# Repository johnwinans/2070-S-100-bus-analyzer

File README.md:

# 2070-S-100-bus-analyzer

A 120 channel S-100 bus logic analyzer

This project is based on the open source ["gusmanb" Logic Analyzer](https://github.com/gusmanb/logicanalyzer) project from Agustín Gimenez Bernad

I have started a [YouTube playlist](https://www.youtube.com/playlist?list=PL3by7evD3F51xCtWdVP3EZzuDttMwDS_U) of videos about this project and my testing of the board.

By using the software from the gusmanb/logicanalyzer repo, a 120 channel logic analyzer can be assembled by installing 5 Raspberry PI PICO boards on this S-100 card and accessed using a USB cables to a PC and/or WiFi as described in the above gusmanb github project Wiki.

Here is a [CSV of the project BOM](./2070-S-100-bus-analyzer.csv) with Digikey order numbers. 

NOTE: I used generic male-headers that I got on Amazon and snapped to length.  I only use gold-plated headers.  Anything else is annoying.
Here is a link to the type that I use for most everything: https://a.co/d/02YRvqt7 (Hint: I snap them to length using a flat [Hakko Wire Cutters](https://a.co/d/055L9axg). Then use shunts to hold them in pairs, triples, or whatever you need so they stay straight and aligned when soldering.)

# Rev 1.0

***NOTICE: As of April 20, 2026 Rev 1.0 of this design has been tested and is a fully functional board.  However, I am making some cosmetic tweaks (silkscreen, better testpoints, and I might shorten the PCB by 1/8"... see my self-critique in the above playlist.)  I will post a release (and remove this message) when I consider it in final form.***

# Rev 2.0

***NOTE: This is a release in progress.  It has not yet been tested.***

## Changes
- Change the board height to 5.0 inches to better fit into IEEE card cages.
- Change to use 3-row headers so that signals can be connected to a trigger input at the same time as the normal analyzedr channel with simpler jumper wires.
- Remove the alternate regulator option.
- Add special headers for pins 20 and 70 to make their purpose more obvious.
- Change to use thru-hole ground test-points for easier use with gator-clips.
- Use larger fonts and better-center the signal names.

# Ordering from JLCPCB

Last time I ordered these, right or wrong, I used these JLCPCB settings:

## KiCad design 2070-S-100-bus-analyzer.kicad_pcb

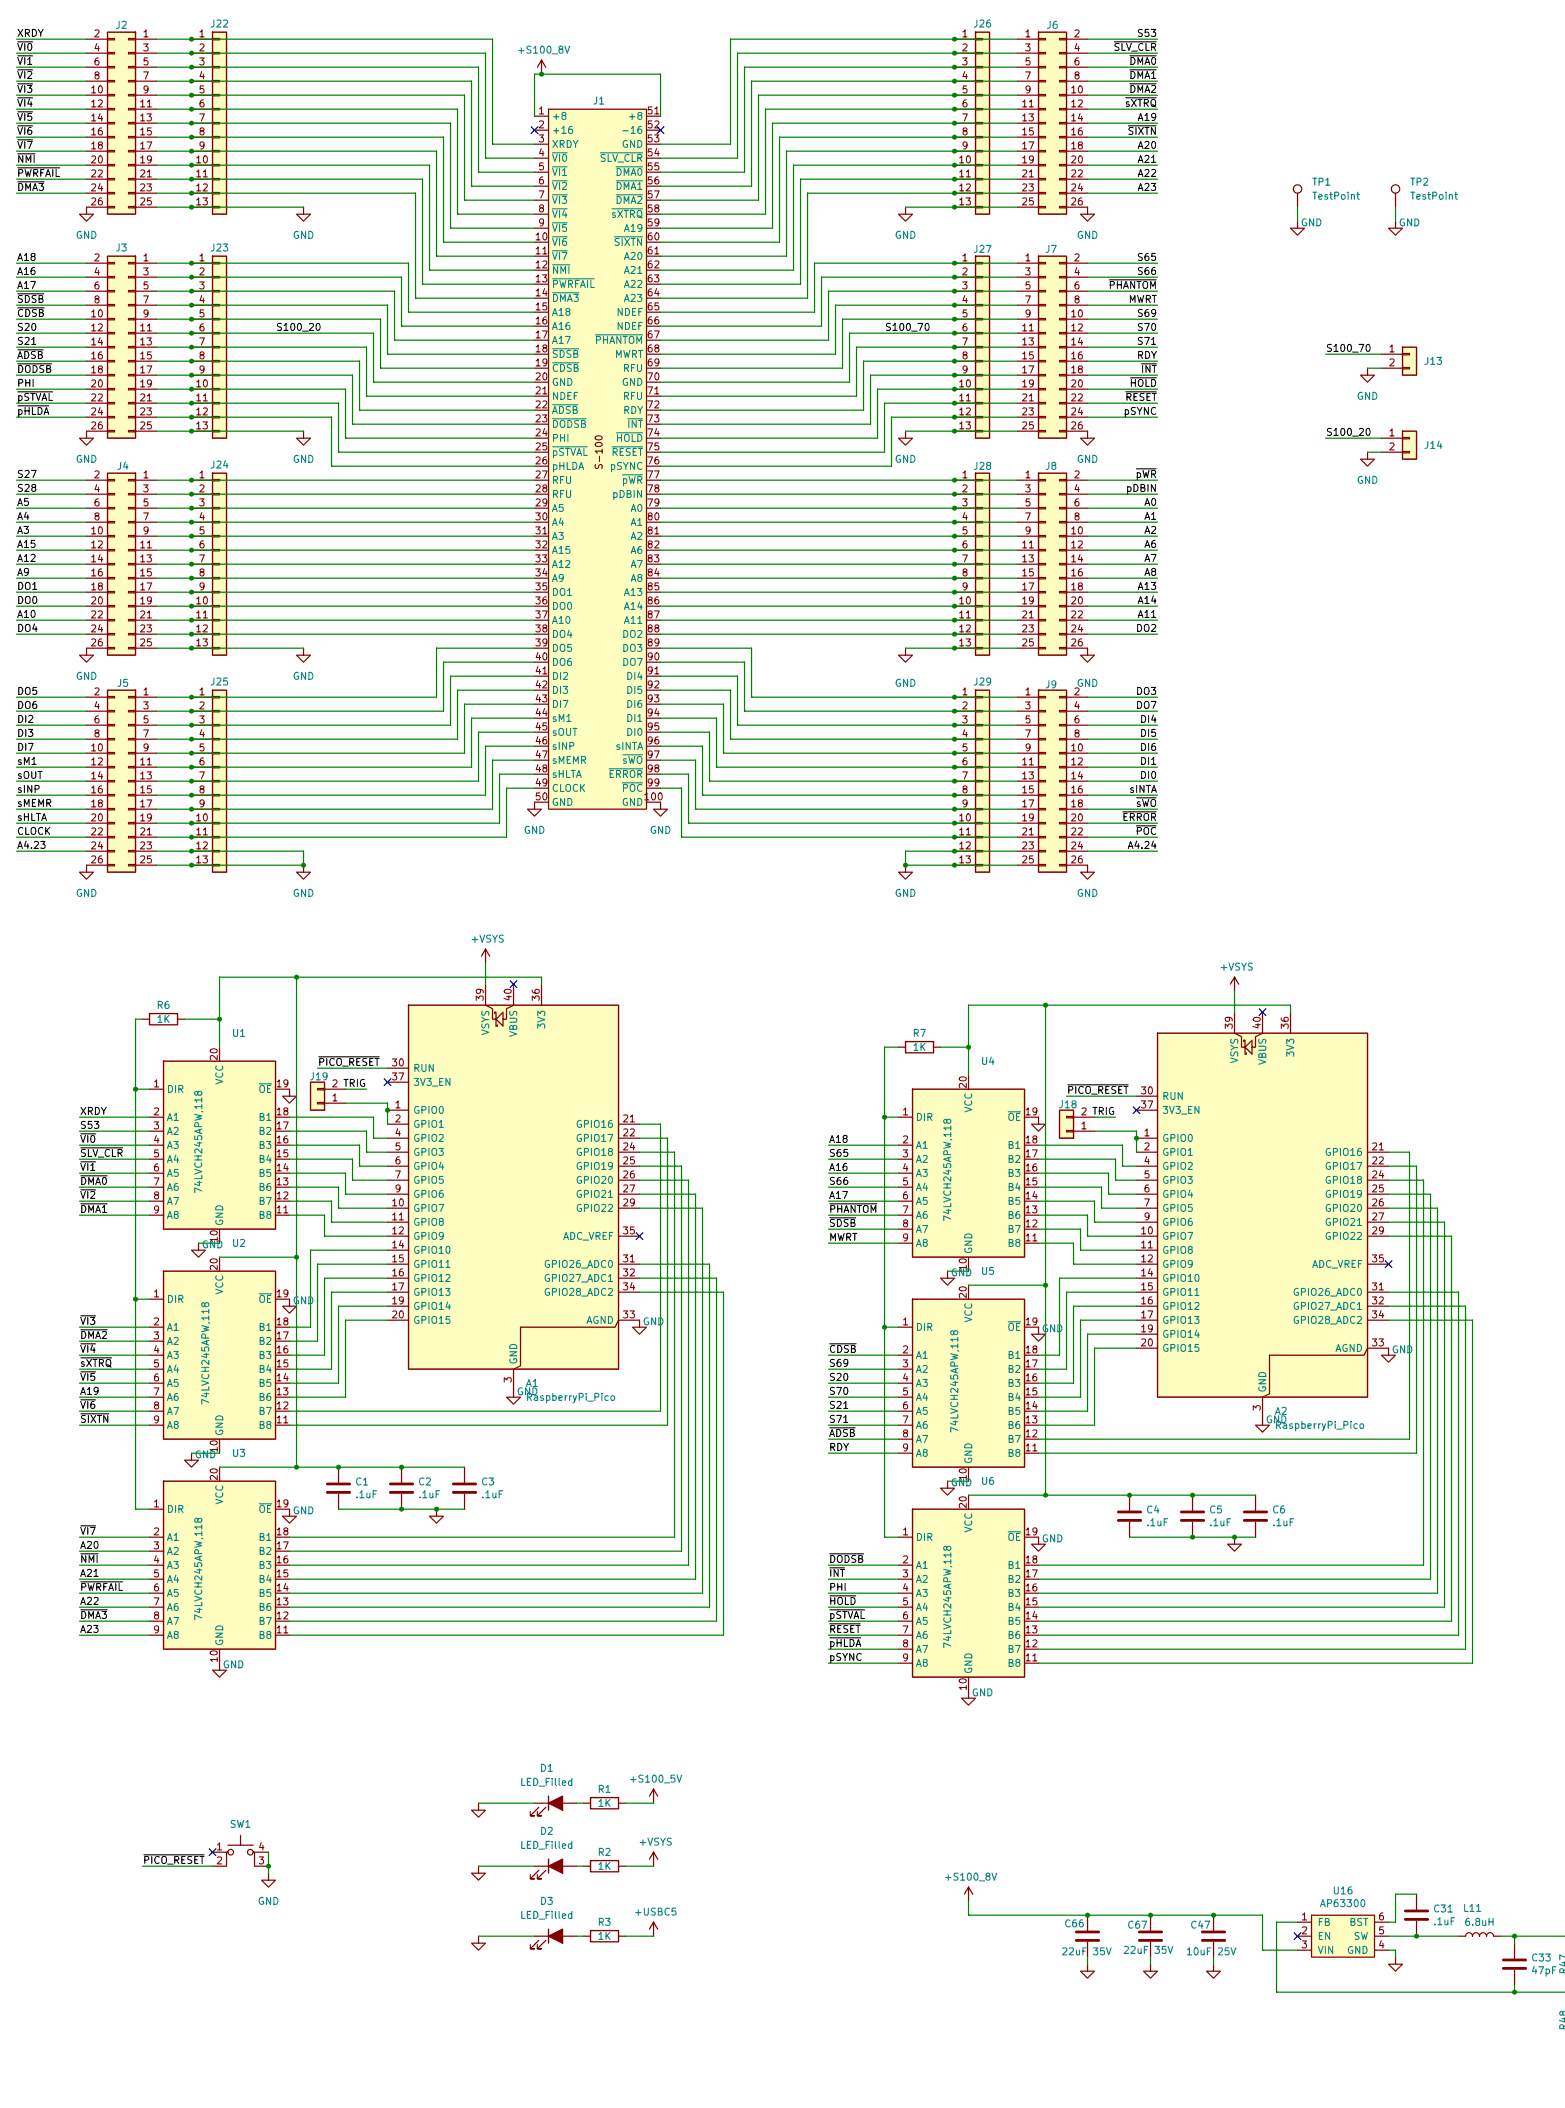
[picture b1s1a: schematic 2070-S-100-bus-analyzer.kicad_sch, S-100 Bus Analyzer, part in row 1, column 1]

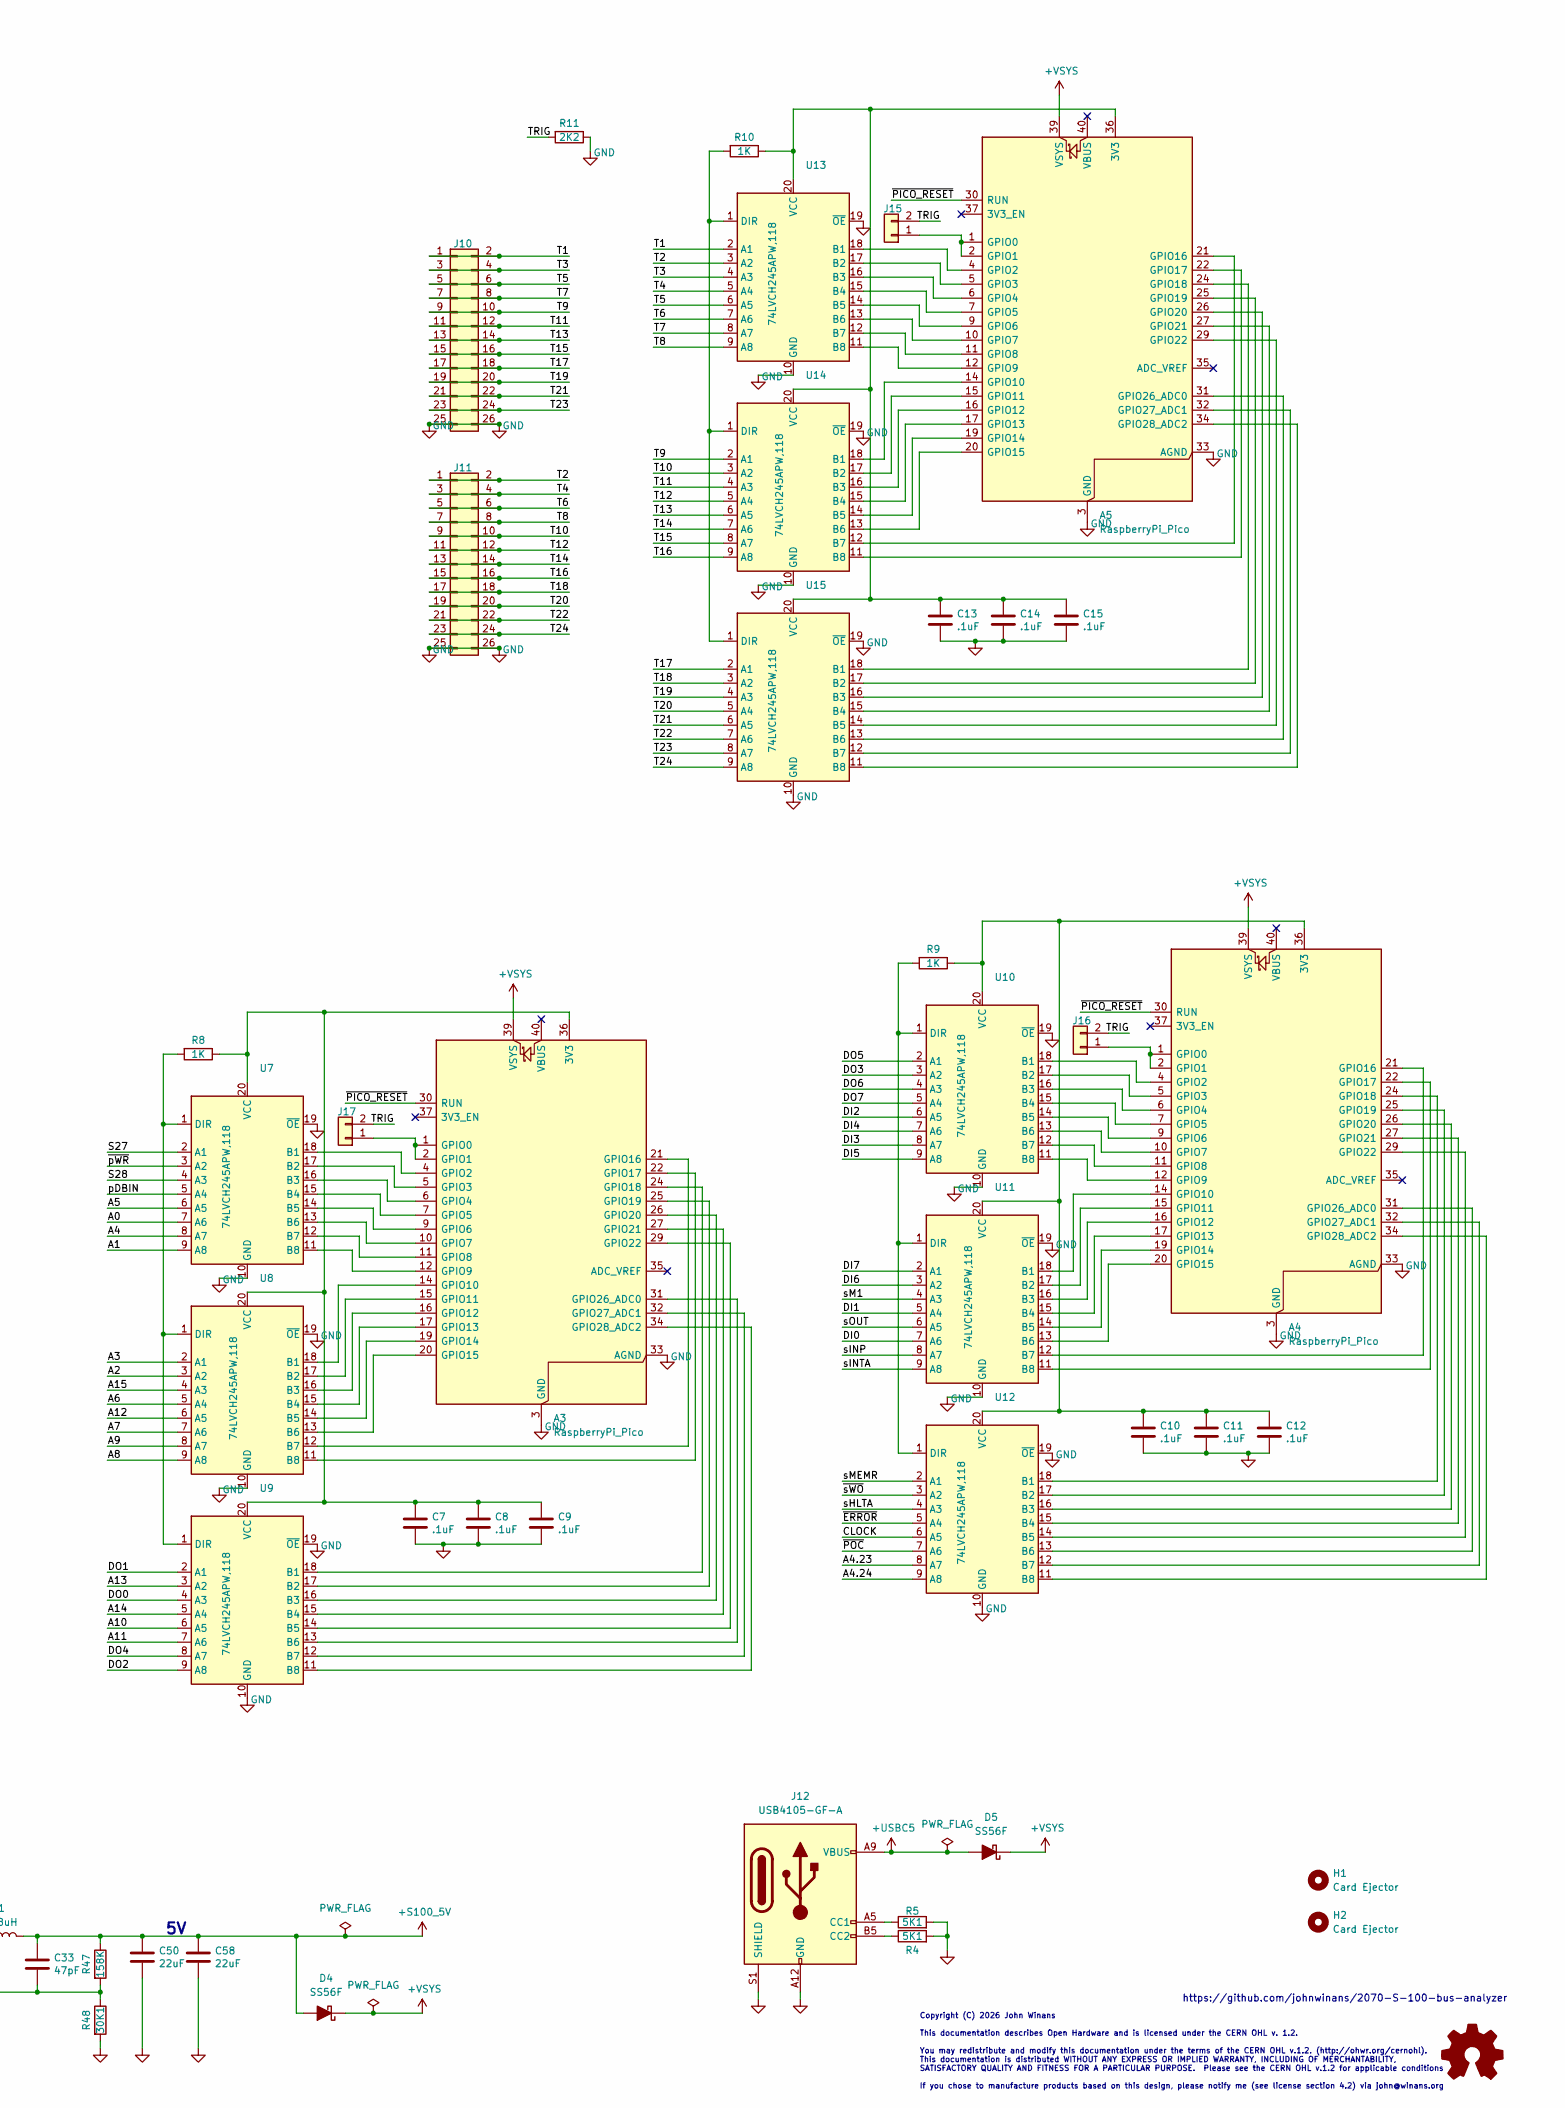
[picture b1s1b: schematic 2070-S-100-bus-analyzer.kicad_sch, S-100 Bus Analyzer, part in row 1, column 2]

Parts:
A1, A2, A3, A4, A5: RaspberryPi_Pico; RaspberryPi_Pico_Common_Unspecified; MPN 2648-SC1631CT-ND; Digi-Key_PN 2648-SC1631CT-ND
C1, C2, C3, C4, C5, C6, C7, C8, C9, C10, C11, C12, C13, C14, C15, C31: .1uF; C_0603_1608Metric_Pad1.08x0.95mm_HandSolder; MPN C1608X5R1E104K; Digi-Key_PN 445-6854-1-ND
C33: 47pF; C_0603_1608Metric_Pad1.08x0.95mm_HandSolder; MPN CL10C470JB8NNNC; Digi-Key_PN 1276-1037-1-ND
C47: 10uF 25V; C_0805_2012Metric_Pad1.18x1.45mm_HandSolder; MPN TMK212BBJ106KG-T; Digi-Key_PN 587-2985-1-ND
C50, C58: 22uF; C_0805_2012Metric_Pad1.18x1.45mm_HandSolder; MPN GRM21BR61A226ME44L; Digi-Key_PN 490-10746-1-ND
C66, C67: 22uF 35V; C_0805_2012Metric_Pad1.18x1.45mm_HandSolder; MPN C2012X5R1V226M125AC; Digi-Key_PN 445-14428-1-ND
D1, D2, D3: LED_Filled; LED_0805_2012Metric_Pad1.15x1.40mm_HandSolder; MPN LG R971-KN-1-0-20-R18; Digi-Key_PN 475-LGR971-KN-1CT-ND
D4, D5: SS56F; D_SMB; MPN SS56F; Digi-Key_PN 5399-SS56FCT-ND
H1, H2: Card Ejector; MountingHole_2.5mm; MPN CP-26 WE; Digi-Key_PN 492-1025-ND
J1: S-100 Edge Connector; S100-Edge-Connector
J2, J3, J4, J5, J6, J7, J8, J9, J10, J11: Conn_02x13_Odd_Even; PinHeader_2x13_P2.54mm_Vertical
J12: USB4105-GF-A; USB_C_Receptacle_GCT_USB4105-xx-A_16P_TopMnt_Horizontal; MPN USB4105-GF-A; Digi-Key_PN 2073-USB4105-GF-ACT-ND
J13, J14, J15, J16, J17, J18, J19: Conn_01x02; PinHeader_1x02_P2.54mm_Vertical
J22, J23, J24, J25, J26, J27, J28, J29: Conn_01x13; PinHeader_1x13_P2.54mm_Vertical
L11: 6.8uH; L_Bourns-SRN6028; MPN VLS6045EX-6R8M; Digi-Key_PN 445-173057-1-ND
LOGO1: OSHW_Logo; OSHW-Logo_11.4x12mm_SilkScreen
R1, R2, R3, R6, R7, R8, R9, R10: 1K; R_0603_1608Metric_Pad0.98x0.95mm_HandSolder; MPN RC0603FR-071KL; Digi-Key_PN 311-1.00KHRCT-ND
R4, R5: 5K1; R_0603_1608Metric_Pad0.98x0.95mm_HandSolder; MPN CR0603-FX-5110ELF; Digi-Key_PN CR0603-FX-510ELFCT-ND
R11: 2K2; R_0603_1608Metric_Pad0.98x0.95mm_HandSolder; MPN RC0603FR-072K2L; Digi-Key_PN 311-2.20KHRCT-ND
R47: 158K; R_0603_1608Metric_Pad0.98x0.95mm_HandSolder; MPN RT0603FRE07158KL; Digi-Key_PN 13-RT0603FRE07158KLCT-ND
R48: 30K1; R_0603_1608Metric_Pad0.98x0.95mm_HandSolder; MPN RT0603FRE0730K1L; Digi-Key_PN 13-RT0603FRE0730K1LCT-ND
SW1: SW_MEC_5E; tactile; MPN 1-1825910-5; Digi-Key_PN 450-1940-ND
TP1, TP2: TestPoint; TestPoint_Keystone_5010-5014_Multipurpose; Digi-Key_PN 2019-RCWCTECT-ND
U1, U2, U3, U4, U5, U6, U7, U8, U9, U10, U11, U12, U13, U14, U15: 74LVCH245APW,118; TSSOP-20_4.4x6.5mm_P0.65mm; MPN 74LVCH245APW,118; Digi-Key_PN 1727-4041-1-ND
U16: AP63300; SOT-23-6; MPN AP63301WU-7; Digi-Key_PN 31-AP63301WU-7CT-ND

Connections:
+S100_5V: C33.1, C50.1, C58.1, D4.2 (A), L11.2, R1.1, R47.1
+S100_8V: C47.1, C66.1, C67.1, J1.1 (+8), J1.51 (+8), U16.3 (VIN)
+USBC5: D5.2 (A), J12.A4 (VBUS), J12.A9 (VBUS), J12.B4 (VBUS), J12.B9 (VBUS), R3.1
+VSYS: A1.39 (VSYS), A2.39 (VSYS), A3.39 (VSYS), A4.39 (VSYS), A5.39 (VSYS), D4.1 (K), D5.1 (K), R2.1
/A0: J8.6, U7.7 (A6)
/A1: J8.8, U7.9 (A8)
/A2: J8.10, U8.3 (A2)
/A3: J4.10, U8.2 (A1)
/A4: J4.8, U7.8 (A7)
/A4.23: J5.24, U12.8 (A7)
/A4.24: J9.24, U12.9 (A8)
/A5: J4.6, U7.6 (A5)
/A6: J8.12, U8.5 (A4)
/A7: J8.14, U8.7 (A6)
/A8: J8.16, U8.9 (A8)
/A9: J4.16, U8.8 (A7)
/A10: J4.22, U9.6 (A5)
/A11: J8.22, U9.7 (A6)
/A12: J4.14, U8.6 (A5)
/A13: J8.18, U9.3 (A2)
/A14: J8.20, U9.5 (A4)
/A15: J4.12, U8.4 (A3)
/A16: J3.4, U4.4 (A3)
/A17: J3.6, U4.6 (A5)
/A18: J3.2, U4.2 (A1)
/A19: J6.14, U2.7 (A6)
/A20: J6.18, U3.3 (A2)
/A21: J6.20, U3.5 (A4)
/A22: J6.22, U3.7 (A6)
/A23: J6.24, U3.9 (A8)
/CLOCK: J5.22, U12.6 (A5)
/DI0: J9.14, U11.7 (A6)
/DI1: J9.12, U11.5 (A4)
/DI2: J5.6, U10.6 (A5)
/DI3: J5.8, U10.8 (A7)
/DI4: J9.6, U10.7 (A6)
/DI5: J9.8, U10.9 (A8)
/DI6: J9.10, U11.3 (A2)
/DI7: J5.10, U11.2 (A1)
/DO0: J4.20, U9.4 (A3)
/DO1: J4.18, U9.2 (A1)
/DO2: J8.24, U9.9 (A8)
/DO3: J9.2, U10.3 (A2)
/DO4: J4.24, U9.8 (A7)
/DO5: J5.2, U10.2 (A1)
/DO6: J5.4, U10.4 (A3)
/DO7: J9.4, U10.5 (A4)
/MWRT: J7.8, U4.9 (A8)
/PHI: J3.20, U6.4 (A3)
/RDY: J7.16, U5.9 (A8)
/S20: J3.12, U5.4 (A3)
/S21: J3.14, U5.6 (A5)
/S27: J4.2, U7.2 (A1)
/S28: J4.4, U7.4 (A3)
/S53: J6.2, U1.3 (A2)
/S65: J7.2, U4.3 (A2)
/S66: J7.4, U4.5 (A4)
/S69: J7.10, U5.3 (A2)
/S70: J7.12, U5.5 (A4)
/S71: J7.14, U5.7 (A6)
/S100_20: J1.20 (GND), J3.11, J14.1, J23.6
/S100_70: J1.70 (GND), J7.11, J13.1, J27.6
/T1: J10.1, J10.2, U13.2 (A1)
/T2: J11.1, J11.2, U13.3 (A2)
/T3: J10.3, J10.4, U13.4 (A3)
/T4: J11.3, J11.4, U13.5 (A4)
/T5: J10.5, J10.6, U13.6 (A5)
/T6: J11.5, J11.6, U13.7 (A6)
/T7: J10.7, J10.8, U13.8 (A7)
/T8: J11.7, J11.8, U13.9 (A8)
/T9: J10.9, J10.10, U14.2 (A1)
/T10: J11.9, J11.10, U14.3 (A2)
/T11: J10.11, J10.12, U14.4 (A3)
/T12: J11.11, J11.12, U14.5 (A4)
/T13: J10.13, J10.14, U14.6 (A5)
/T14: J11.13, J11.14, U14.7 (A6)
/T15: J10.15, J10.16, U14.8 (A7)
/T16: J11.15, J11.16, U14.9 (A8)
/T17: J10.17, J10.18, U15.2 (A1)
/T18: J11.17, J11.18, U15.3 (A2)
/T19: J10.19, J10.20, U15.4 (A3)
/T20: J11.19, J11.20, U15.5 (A4)
/T21: J10.21, J10.22, U15.6 (A5)
/T22: J11.21, J11.22, U15.7 (A6)
/T23: J10.23, J10.24, U15.8 (A7)
/T24: J11.23, J11.24, U15.9 (A8)
/TRIG: J15.2, J16.2, J17.2, J18.2, J19.2, R11.2
/XRDY: J2.2, U1.2 (A1)
/pDBIN: J8.4, U7.5 (A4)
/pSYNC: J7.24, U6.9 (A8)
/sHLTA: J5.20, U12.4 (A3)
/sINP: J5.16, U11.8 (A7)
/sINTA: J9.16, U11.9 (A8)
/sM1: J5.12, U11.4 (A3)
/sMEMR: J5.18, U12.2 (A1)
/sOUT: J5.14, U11.6 (A5)
/~ADSB: J3.16, U5.8 (A7)
/~CDSB: J3.10, U5.2 (A1)
/~DMA0: J6.6, U1.7 (A6)
/~DMA1: J6.8, U1.9 (A8)
/~DMA2: J6.10, U2.3 (A2)
/~DMA3: J2.24, U3.8 (A7)
/~DODSB: J3.18, U6.2 (A1)
/~ERROR: J9.20, U12.5 (A4)
/~HOLD: J7.20, U6.5 (A4)
/~INT: J7.18, U6.3 (A2)
/~NMI: J2.20, U3.4 (A3)
/~PHANTOM: J7.6, U4.7 (A6)
/~PICO_RESET: A1.30 (RUN), A2.30 (RUN), A3.30 (RUN), A4.30 (RUN), A5.30 (RUN), SW1.2
/~POC: J9.22, U12.7 (A6)
/~PWRFAIL: J2.22, U3.6 (A5)
/~RESET: J7.22, U6.7 (A6)
/~SDSB: J3.8, U4.8 (A7)
/~SIXTN: J6.16, U2.9 (A8)
/~SLV_CLR: J6.4, U1.5 (A4)
/~VI0: J2.4, U1.4 (A3)
/~VI1: J2.6, U1.6 (A5)
/~VI2: J2.8, U1.8 (A7)
/~VI3: J2.10, U2.2 (A1)
/~VI4: J2.12, U2.4 (A3)
/~VI5: J2.14, U2.6 (A5)
/~VI6: J2.16, U2.8 (A7)
/~VI7: J2.18, U3.2 (A1)
/~pHLDA: J3.24, U6.8 (A7)
/~pSTVAL: J3.22, U6.6 (A5)
/~pWR: J8.2, U7.3 (A2)
/~sWO: J9.18, U12.3 (A2)
/~sXTRQ: J6.12, U2.5 (A4)
GND: A1.3 (GND), A1.8 (GND), A1.13 (GND), A1.18 (GND), A1.23 (GND), A1.28 (GND), A1.33 (AGND), A1.38 (GND), A2.3 (GND), A2.8 (GND), A2.13 (GND), A2.18 (GND), A2.23 (GND), A2.28 (GND), A2.33 (AGND), A2.38 (GND), A3.3 (GND), A3.8 (GND), A3.13 (GND), A3.18 (GND), A3.23 (GND), A3.28 (GND), A3.33 (AGND), A3.38 (GND), A4.3 (GND), A4.8 (GND), A4.13 (GND), A4.18 (GND), A4.23 (GND), A4.28 (GND), A4.33 (AGND), A4.38 (GND), A5.3 (GND), A5.8 (GND), A5.13 (GND), A5.18 (GND), A5.23 (GND), A5.28 (GND), A5.33 (AGND), A5.38 (GND), C1.2, C2.2, C3.2, C4.2, C5.2, C6.2, C7.2, C8.2, C9.2, C10.2, C11.2, C12.2, C13.2, C14.2, C15.2, C47.2, C50.2, C58.2, C66.2, C67.2, D1.1 (K), D2.1 (K), D3.1 (K), J1.50 (GND), J1.100 (GND), J2.25, J2.26, J3.25, J3.26, J4.25, J4.26, J5.23, J5.25, J5.26, J6.25, J6.26, J7.25, J7.26, J8.25, J8.26, J9.23, J9.25, J9.26, J10.25, J10.26, J11.25, J11.26, J12.A1 (GND), J12.A12 (GND), J12.B1 (GND), J12.B12 (GND), J12.S1 (SHIELD), J13.2, J14.2, J22.13, J23.13, J24.13, J25.12, J25.13, J26.13, J27.13, J28.13, J29.12, J29.13, R4.2, R5.2, R11.1, R48.2, SW1.3 (K), SW1.4 (A), TP1.1, TP2.1, U1.10 (GND), U1.19 (~OE), U2.10 (GND), U2.19 (~OE), U3.10 (GND), U3.19 (~OE), U4.10 (GND), U4.19 (~OE), U5.10 (GND), U5.19 (~OE), U6.10 (GND), U6.19 (~OE), U7.10 (GND), U7.19 (~OE), U8.10 (GND), U8.19 (~OE), U9.10 (GND), U9.19 (~OE), U10.10 (GND), U10.19 (~OE), U11.10 (GND), U11.19 (~OE), U12.10 (GND), U12.19 (~OE), U13.10 (GND), U13.19 (~OE), U14.10 (GND), U14.19 (~OE), U15.10 (GND), U15.19 (~OE), U16.4 (GND)
unnamed: A1.36 (3V3), C1.1, C2.1, C3.1, R6.1, U1.20 (VCC), U2.20 (VCC), U3.20 (VCC)
unnamed: A1.1 (GPIO0), A1.2 (GPIO1), J19.1
unnamed: A1.4 (GPIO2), U1.18 (B1)
unnamed: A1.5 (GPIO3), U1.17 (B2)
unnamed: A1.6 (GPIO4), U1.16 (B3)
unnamed: A1.7 (GPIO5), U1.15 (B4)
unnamed: A1.9 (GPIO6), U1.14 (B5)
unnamed: A1.10 (GPIO7), U1.13 (B6)
unnamed: A1.11 (GPIO8), U1.12 (B7)
unnamed: A1.12 (GPIO9), U1.11 (B8)
unnamed: A1.14 (GPIO10), U2.18 (B1)
unnamed: A1.15 (GPIO11), U2.17 (B2)
unnamed: A1.16 (GPIO12), U2.16 (B3)
unnamed: A1.17 (GPIO13), U2.15 (B4)
unnamed: A1.19 (GPIO14), U2.14 (B5)
unnamed: A1.20 (GPIO15), U2.13 (B6)
unnamed: A1.21 (GPIO16), U2.12 (B7)
unnamed: A1.22 (GPIO17), U2.11 (B8)
unnamed: A1.24 (GPIO18), U3.18 (B1)
unnamed: A1.25 (GPIO19), U3.17 (B2)
unnamed: A1.26 (GPIO20), U3.16 (B3)
unnamed: A1.27 (GPIO21), U3.15 (B4)
unnamed: A1.29 (GPIO22), U3.14 (B5)
unnamed: A1.31 (GPIO26_ADC0), U3.13 (B6)
unnamed: A1.32 (GPIO27_ADC1), U3.12 (B7)
unnamed: A1.34 (GPIO28_ADC2), U3.11 (B8)
unnamed: A2.36 (3V3), C4.1, C5.1, C6.1, R7.1, U4.20 (VCC), U5.20 (VCC), U6.20 (VCC)
unnamed: A2.1 (GPIO0), A2.2 (GPIO1), J18.1
unnamed: A2.4 (GPIO2), U4.18 (B1)
unnamed: A2.5 (GPIO3), U4.17 (B2)
unnamed: A2.6 (GPIO4), U4.16 (B3)
unnamed: A2.7 (GPIO5), U4.15 (B4)
unnamed: A2.9 (GPIO6), U4.14 (B5)
unnamed: A2.10 (GPIO7), U4.13 (B6)
unnamed: A2.11 (GPIO8), U4.12 (B7)
unnamed: A2.12 (GPIO9), U4.11 (B8)
unnamed: A2.14 (GPIO10), U5.18 (B1)
unnamed: A2.15 (GPIO11), U5.17 (B2)
unnamed: A2.16 (GPIO12), U5.16 (B3)
unnamed: A2.17 (GPIO13), U5.15 (B4)
unnamed: A2.19 (GPIO14), U5.14 (B5)
unnamed: A2.20 (GPIO15), U5.13 (B6)
unnamed: A2.21 (GPIO16), U5.12 (B7)
unnamed: A2.22 (GPIO17), U5.11 (B8)
unnamed: A2.24 (GPIO18), U6.18 (B1)
unnamed: A2.25 (GPIO19), U6.17 (B2)
unnamed: A2.26 (GPIO20), U6.16 (B3)
unnamed: A2.27 (GPIO21), U6.15 (B4)
unnamed: A2.29 (GPIO22), U6.14 (B5)
unnamed: A2.31 (GPIO26_ADC0), U6.13 (B6)
unnamed: A2.32 (GPIO27_ADC1), U6.12 (B7)
unnamed: A2.34 (GPIO28_ADC2), U6.11 (B8)
unnamed: A3.36 (3V3), C7.1, C8.1, C9.1, R8.1, U7.20 (VCC), U8.20 (VCC), U9.20 (VCC)
unnamed: A3.1 (GPIO0), A3.2 (GPIO1), J17.1
unnamed: A3.4 (GPIO2), U7.18 (B1)
unnamed: A3.5 (GPIO3), U7.17 (B2)
unnamed: A3.6 (GPIO4), U7.16 (B3)
unnamed: A3.7 (GPIO5), U7.15 (B4)
unnamed: A3.9 (GPIO6), U7.14 (B5)
unnamed: A3.10 (GPIO7), U7.13 (B6)
unnamed: A3.11 (GPIO8), U7.12 (B7)
unnamed: A3.12 (GPIO9), U7.11 (B8)
unnamed: A3.14 (GPIO10), U8.18 (B1)
unnamed: A3.15 (GPIO11), U8.17 (B2)
unnamed: A3.16 (GPIO12), U8.16 (B3)
unnamed: A3.17 (GPIO13), U8.15 (B4)
unnamed: A3.19 (GPIO14), U8.14 (B5)
unnamed: A3.20 (GPIO15), U8.13 (B6)
unnamed: A3.21 (GPIO16), U8.12 (B7)
unnamed: A3.22 (GPIO17), U8.11 (B8)
unnamed: A3.24 (GPIO18), U9.18 (B1)
unnamed: A3.25 (GPIO19), U9.17 (B2)
unnamed: A3.26 (GPIO20), U9.16 (B3)
unnamed: A3.27 (GPIO21), U9.15 (B4)
unnamed: A3.29 (GPIO22), U9.14 (B5)
unnamed: A3.31 (GPIO26_ADC0), U9.13 (B6)
unnamed: A3.32 (GPIO27_ADC1), U9.12 (B7)
unnamed: A3.34 (GPIO28_ADC2), U9.11 (B8)
unnamed: A4.36 (3V3), C10.1, C11.1, C12.1, R9.1, U10.20 (VCC), U11.20 (VCC), U12.20 (VCC)
unnamed: A4.1 (GPIO0), A4.2 (GPIO1), J16.1
unnamed: A4.4 (GPIO2), U10.18 (B1)
unnamed: A4.5 (GPIO3), U10.17 (B2)
unnamed: A4.6 (GPIO4), U10.16 (B3)
unnamed: A4.7 (GPIO5), U10.15 (B4)
unnamed: A4.9 (GPIO6), U10.14 (B5)
unnamed: A4.10 (GPIO7), U10.13 (B6)
unnamed: A4.11 (GPIO8), U10.12 (B7)
unnamed: A4.12 (GPIO9), U10.11 (B8)
unnamed: A4.14 (GPIO10), U11.18 (B1)
unnamed: A4.15 (GPIO11), U11.17 (B2)
unnamed: A4.16 (GPIO12), U11.16 (B3)
unnamed: A4.17 (GPIO13), U11.15 (B4)
unnamed: A4.19 (GPIO14), U11.14 (B5)
unnamed: A4.20 (GPIO15), U11.13 (B6)
unnamed: A4.21 (GPIO16), U11.12 (B7)
unnamed: A4.22 (GPIO17), U11.11 (B8)
unnamed: A4.24 (GPIO18), U12.18 (B1)
unnamed: A4.25 (GPIO19), U12.17 (B2)
unnamed: A4.26 (GPIO20), U12.16 (B3)
unnamed: A4.27 (GPIO21), U12.15 (B4)
unnamed: A4.29 (GPIO22), U12.14 (B5)
unnamed: A4.31 (GPIO26_ADC0), U12.13 (B6)
unnamed: A4.32 (GPIO27_ADC1), U12.12 (B7)
unnamed: A4.34 (GPIO28_ADC2), U12.11 (B8)
unnamed: A5.36 (3V3), C13.1, C14.1, C15.1, R10.1, U13.20 (VCC), U14.20 (VCC), U15.20 (VCC)
unnamed: A5.1 (GPIO0), A5.2 (GPIO1), J15.1
unnamed: A5.4 (GPIO2), U13.18 (B1)
unnamed: A5.5 (GPIO3), U13.17 (B2)
unnamed: A5.6 (GPIO4), U13.16 (B3)
unnamed: A5.7 (GPIO5), U13.15 (B4)
unnamed: A5.9 (GPIO6), U13.14 (B5)
unnamed: A5.10 (GPIO7), U13.13 (B6)
unnamed: A5.11 (GPIO8), U13.12 (B7)
unnamed: A5.12 (GPIO9), U13.11 (B8)
unnamed: A5.14 (GPIO10), U14.18 (B1)
unnamed: A5.15 (GPIO11), U14.17 (B2)
unnamed: A5.16 (GPIO12), U14.16 (B3)
unnamed: A5.17 (GPIO13), U14.15 (B4)
unnamed: A5.19 (GPIO14), U14.14 (B5)
unnamed: A5.20 (GPIO15), U14.13 (B6)
unnamed: A5.21 (GPIO16), U14.12 (B7)
unnamed: A5.22 (GPIO17), U14.11 (B8)
unnamed: A5.24 (GPIO18), U15.18 (B1)
unnamed: A5.25 (GPIO19), U15.17 (B2)
unnamed: A5.26 (GPIO20), U15.16 (B3)
unnamed: A5.27 (GPIO21), U15.15 (B4)
unnamed: A5.29 (GPIO22), U15.14 (B5)
unnamed: A5.31 (GPIO26_ADC0), U15.13 (B6)
unnamed: A5.32 (GPIO27_ADC1), U15.12 (B7)
unnamed: A5.34 (GPIO28_ADC2), U15.11 (B8)
unnamed: D1.2 (A), R1.2
unnamed: D2.2 (A), R2.2
unnamed: D3.2 (A), R3.2
unnamed: J1.79 (A0), J8.5, J28.3
unnamed: J1.80 (A1), J8.7, J28.4
unnamed: J1.81 (A2), J8.9, J28.5
unnamed: J1.31 (A3), J4.9, J24.5
unnamed: J1.30 (A4), J4.7, J24.4
unnamed: J1.29 (A5), J4.5, J24.3
unnamed: J1.82 (A6), J8.11, J28.6
unnamed: J1.83 (A7), J8.13, J28.7
unnamed: J1.84 (A8), J8.15, J28.8
unnamed: J1.34 (A9), J4.15, J24.8
unnamed: J1.37 (A10), J4.21, J24.11
unnamed: J1.87 (A11), J8.21, J28.11
unnamed: J1.33 (A12), J4.13, J24.7
unnamed: J1.85 (A13), J8.17, J28.9
unnamed: J1.86 (A14), J8.19, J28.10
unnamed: J1.32 (A15), J4.11, J24.6
unnamed: J1.16 (A16), J3.3, J23.2
unnamed: J1.17 (A17), J3.5, J23.3
unnamed: J1.15 (A18), J3.1, J23.1
unnamed: J1.59 (A19), J6.13, J26.7
unnamed: J1.61 (A20), J6.17, J26.9
unnamed: J1.62 (A21), J6.19, J26.10
unnamed: J1.63 (A22), J6.21, J26.11
unnamed: J1.64 (A23), J6.23, J26.12
unnamed: J1.49 (CLOCK), J5.21, J25.11
unnamed: J1.95 (DI0), J9.13, J29.7
unnamed: J1.94 (DI1), J9.11, J29.6
unnamed: J1.41 (DI2), J5.5, J25.3
unnamed: J1.42 (DI3), J5.7, J25.4
unnamed: J1.91 (DI4), J9.5, J29.3
unnamed: J1.92 (DI5), J9.7, J29.4
unnamed: J1.93 (DI6), J9.9, J29.5
unnamed: J1.43 (DI7), J5.9, J25.5
unnamed: J1.36 (DO0), J4.19, J24.10
unnamed: J1.35 (DO1), J4.17, J24.9
unnamed: J1.88 (DO2), J8.23, J28.12
unnamed: J1.89 (DO3), J9.1, J29.1
unnamed: J1.38 (DO4), J4.23, J24.12
unnamed: J1.39 (DO5), J5.1, J25.1
unnamed: J1.40 (DO6), J5.3, J25.2
unnamed: J1.90 (DO7), J9.3, J29.2
unnamed: J1.68 (MWRT), J7.7, J27.4
unnamed: J1.24 (PHI), J3.19, J23.10
unnamed: J1.72 (RDY), J7.15, J27.8
unnamed: J1.3 (XRDY), J2.1, J22.1
unnamed: J1.78 (pDBIN), J8.3, J28.2
unnamed: J1.26 (pHLDA), J3.23, J23.12
unnamed: J1.76 (pSYNC), J7.23, J27.12
unnamed: J1.48 (sHLTA), J5.19, J25.10
unnamed: J1.46 (sINP), J5.15, J25.8
unnamed: J1.96 (sINTA), J9.15, J29.8
unnamed: J1.44 (sM1), J5.11, J25.6
unnamed: J1.47 (sMEMR), J5.17, J25.9
unnamed: J1.45 (sOUT), J5.13, J25.7
unnamed: J1.22 (~ADSB), J3.15, J23.8
unnamed: J1.19 (~CDSB), J3.9, J23.5
unnamed: J1.55 (~DMA0), J6.5, J26.3
unnamed: J1.56 (~DMA1), J6.7, J26.4
unnamed: J1.57 (~DMA2), J6.9, J26.5
unnamed: J1.14 (~DMA3), J2.23, J22.12
unnamed: J1.23 (~DODSB), J3.17, J23.9
unnamed: J1.98 (~ERROR), J9.19, J29.10
unnamed: J1.74 (~HOLD), J7.19, J27.10
unnamed: J1.73 (~INT), J7.17, J27.9
unnamed: J1.12 (~NMI), J2.19, J22.10
unnamed: J1.67 (~PHANTOM), J7.5, J27.3
unnamed: J1.99 (~POC), J9.21, J29.11
unnamed: J1.13 (~PWRFAIL), J2.21, J22.11
unnamed: J1.75 (~RESET), J7.21, J27.11
unnamed: J1.18 (~SDSB), J3.7, J23.4
unnamed: J1.60 (~SIXTN), J6.15, J26.8
unnamed: J1.54 (~SLV_CLR), J6.3, J26.2
unnamed: J1.4 (~VI0), J2.3, J22.2
unnamed: J1.5 (~VI1), J2.5, J22.3
unnamed: J1.6 (~VI2), J2.7, J22.4
unnamed: J1.7 (~VI3), J2.9, J22.5
unnamed: J1.8 (~VI4), J2.11, J22.6
unnamed: J1.9 (~VI5), J2.13, J22.7
unnamed: J1.10 (~VI6), J2.15, J22.8
unnamed: J1.11 (~VI7), J2.17, J22.9
unnamed: J1.25 (~pSTVAL), J3.21, J23.11
unnamed: J1.77 (~pWR), J8.1, J28.1
unnamed: J1.97 (~sWO), J9.17, J29.9
unnamed: J1.58 (~sXTRQ), J6.11, J26.6
unnamed: J12.A5 (CC1), R5.1
unnamed: J12.B5 (CC2), R4.1
unnamed: J1.21 (NDEF), J3.13, J23.7
unnamed: J1.27 (RFU), J4.1, J24.1
unnamed: J1.28 (RFU), J4.3, J24.2
unnamed: J1.53 (GND), J6.1, J26.1
unnamed: J1.65 (NDEF), J7.1, J27.1
unnamed: J1.66 (NDEF), J7.3, J27.2
unnamed: J1.69 (RFU), J7.9, J27.5
unnamed: J1.71 (RFU), J7.13, J27.7
unnamed: R6.2, U1.1 (DIR), U2.1 (DIR), U3.1 (DIR)
unnamed: R7.2, U4.1 (DIR), U5.1 (DIR), U6.1 (DIR)
unnamed: R8.2, U7.1 (DIR), U8.1 (DIR), U9.1 (DIR)
unnamed: R9.2, U10.1 (DIR), U11.1 (DIR), U12.1 (DIR)
unnamed: R10.2, U13.1 (DIR), U14.1 (DIR), U15.1 (DIR)
unnamed: C31.1, U16.6 (BST)
unnamed: C33.2, R47.2, R48.1, U16.1 (FB)
unnamed: C31.2, L11.1, U16.5 (SW)

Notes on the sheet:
https://github.com/johnwinans/2070-S-100-bus-analyzer
Copyright (C) 2026 John Winans This documentation describes Open Hardware and is licensed under the CERN OHL v. 1.2. You may redistribute and modify this documentation under the terms of the CERN OHL v.1.2. (http://ohwr.org/cernohl). This documentation is distributed WITHOUT ANY EXPRESS OR IMPLIED 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

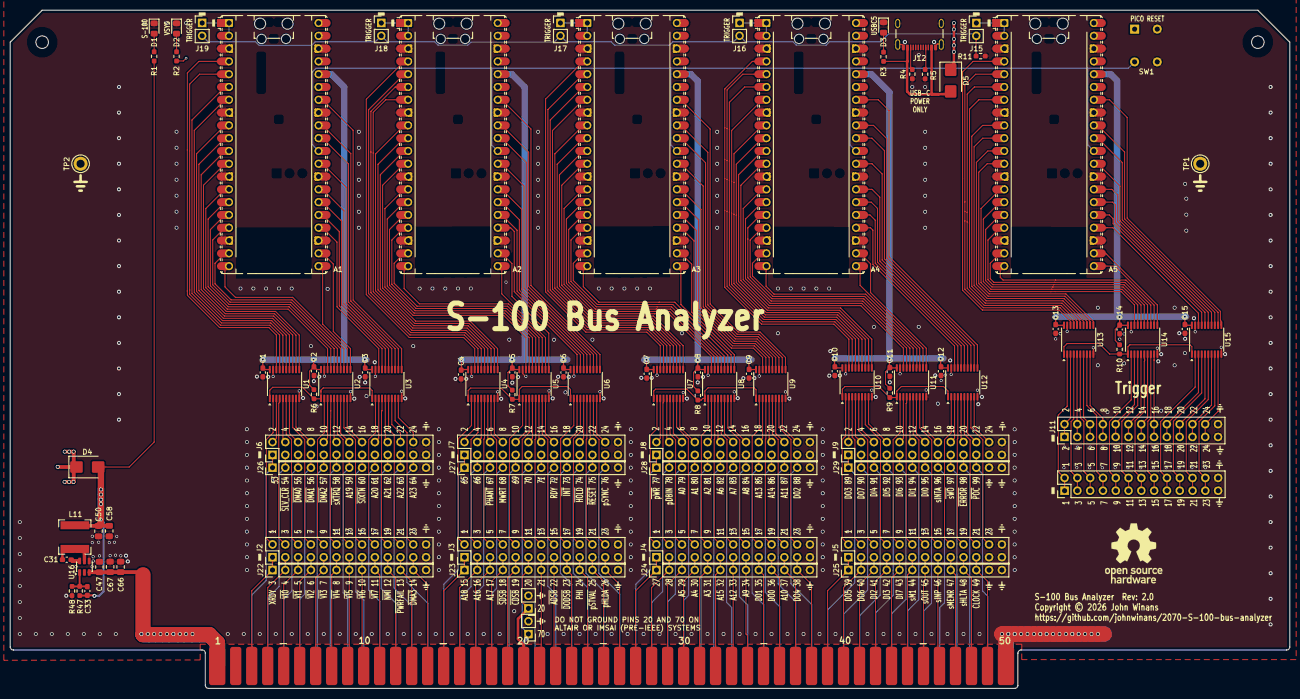
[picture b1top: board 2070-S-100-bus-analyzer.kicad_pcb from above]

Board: 4 copper layers, 254.0 x 134.6 mm, 96 parts (1 on the bottom side), 364 nets.

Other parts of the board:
LOGO1#2: OSHW_Logo; OSHW-Logo_11.4x12mm_SilkScreen

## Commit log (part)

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2026-03-01 Ignore noise
2026-03-01 Import S-100 template
2026-03-01 Add image
2026-03-15 Re-start project from new KiCad9 S-100 template
2026-03-21 Checkpoint
2026-03-21 Add S100 power
2026-03-24 Acute angles Remove paste from J1 Teardrops
2026-03-24 Acute angles
2026-03-25 Rounded edge fingers curved teardrops improve finger edge clearance
2026-03-25 DRC cleanup on edge fingers
2026-03-25 DRC cleanup
2026-03-25 power supply routing
2026-03-26 DRC fixes Clean up power supplies
2026-03-27 Add title block
2026-03-27 update power supply as per wiggle
2026-03-27 Add pin-1 markers
2026-03-28 cosmetic stuff add gnd stiching vias
2026-03-30 Remove OSHW from BOM
2026-03-31 BOM updates
2026-04-09 Correct spelling of PHI :-D
2026-04-19 Change trigger pulldown to 2.2K
2026-04-19 Rename /pDBIN as pDBIN & update silk
2026-04-19 Change /pSYNC to pSYNC & fix silk Larger testoints for gators
2026-04-21 Add some part info
2026-05-07 Remove linear regulator option
2026-05-08 Add 3rd header row, note pins20/70, fonts, BOM
2026-05-17 C capture app proof of concept (Linux only.)
2026-05-20 Set channel numbers in capture msg clean up debugging output
2026-05-21 Imported from https://github.com/gusmanb/logicanalyzer/tree/version/v6_5/Firmware/LogicAnalyzer_V2
2026-05-21 add a README
2026-05-21 Config for PICO2, no TURBO
2026-05-21 Normalize line endings to LF
2026-05-21 Fix messageBuffer overrun Message block resync fix Speed up main loop by flashing LED faster
2026-05-23 Implement DTR & RTS flags
2026-05-24 fix broken DTR RTS
2026-05-24 Reverse printing order of CSV output

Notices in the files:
2070-S-100-bus-analyzer.kicad_pcb:
Copyright © 2026 John Winans
2070-S-100-bus-analyzer.kicad_sch:
If you chose to manufacture products based on this design, please notify me (see license section 4.2) via john@winans.org
